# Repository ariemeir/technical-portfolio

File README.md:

# Technical Portfolio — Arie Meir

Representative projects, published for reference.

**→ [Browse all source on GitHub](https://github.com/ariemeir/technical-portfolio)**

## Projects

### [RoboImplant](roboimplant/) — non-invasive spinal implant adjustment system

A motorized orthopedic implant that lengthens a spinal distraction rod without
surgery, for treating early-onset scoliosis in growing children. Full-stack
across four disciplines:

- **Embedded** — AVR C firmware on an ATmega1284P: real-time motor control via a
  DS1267 digital pot into a maxon ESCON servo controller, interrupt-driven
  rotation counting, and current-threshold coupling detection as the primary
  safety interlock.
- **Mobile** — Android clinician console over Bluetooth SPP, with a custom
  line-oriented ASCII protocol, live telemetry, 3D visualization, and patient
  records.
- **Electronics** — EAGLE schematic and board layout for the controller,
  including the analog current/voltage sensing chain.
- **Mechanical** — SolidWorks enclosure for the handheld driver unit.

<p align="center">
  
  <br>
  <em>The handheld driver unit (v1)</em>
</p>

**→ [Read the one-page case study (PDF)](roboimplant/docs/roboimplant-case-study-arie-meir.pdf)**

Research prototype, ~2012–2013. Not a cleared medical device.
See [`roboimplant/NOTICE.md`](roboimplant/NOTICE.md) for rights and third-party
attribution.

---

### [3D Scanner](3dscanner/) — turntable photogrammetry rig

A DIY tabletop 3D scanner built to solve a real fabrication problem: an artist needed
larger and deeper variants of a commercially molded clay flower that existed only as a
physical object. It takes that object and produces a printable, watertight STL. Five
subsystems bound together by explicit contracts:

- **iOS** — **ScannerCam**, an iPhone camera server with a hand-rolled HTTP/1.1
  stack on `NWListener`: 13 REST routes, bearer auth with constant-time comparison,
  Keychain token storage, and hard locks on focus, exposure, and white balance.
  SwiftUI + AVFoundation, zero third-party packages.
- **Orchestration** — a Python session controller driving the scan loop across two
  machines, with idempotent retries, resumable sessions, and a five-stage SHA-256
  integrity chain from the phone's memory to the final archive.
- **Embedded** — an Arduino that controls the turntable by *impersonating its
  infrared remote*, replaying NEC codes reverse-engineered with a majority-vote
  capture sketch. No data port, no feedback, no encoder.
- **Reconstruction** — a Swift CLI over Apple Object Capture (RealityKit), chosen
  after COLMAP was tested and rejected for being CUDA-only on Apple Silicon.
- **Print prep** — a PyMeshLab pass that makes the mesh watertight, orients it by
  PCA, and scales it to real millimetres for printing and silicone-mold casting.

<p align="center">
  
  <br>
  <em>Input and output: the original ceramic dish, and a printed reproduction
  scanned from it.</em>
</p>

```
object ─→ 72 photos ─→ pose solve ─→ textured mesh ─→ watertight STL ─→ printed master
          locked        Object          USDZ/OBJ        PyMeshLab         silicone mold
          optics        Capture                         repair            → cast copies
```

The engineering centrepiece is control of an actuator that cannot be observed: the
turntable answers only to a fire-and-forget infrared *toggle*, so the controller
tracks an explicit assumed state and halts for human realignment on any ambiguity
rather than guessing and silently desynchronising the scan.

**→ [Read the one-page case study (PDF)](3dscanner/docs/3dscanner-case-study-arie-meir.pdf)**
· [Engineering log](3dscanner/docs/engineering-log.md)
· [Technical spec](3dscanner/docs/scannercam_spec.md)

Personal project, 2026. Working single-operator rig at late-prototype maturity.
See [`3dscanner/NOTICE.md`](3dscanner/NOTICE.md) for rights and attribution.

---

### [WifeSignal](wifesignal/) — a traffic light for the office door

A three-colour desk lamp that lets one person in the house tell another *how much
this can wait*. The office is a separate building: music on, windows closed, phone
face-down and unchecked for hours — which is the point, and which makes it a sealed
box. Text-and-hope fails when it matters; walking over always costs an interruption
whether or not the thing was urgent. The missing piece was never notification, it
was **priority expressed before the interruption happens**. Five components across
four disciplines:

- **iOS** — a SwiftUI app in 333 lines with no third-party packages and no
  Bluetooth: three priority buttons, a 5 s status poll, and a *Waiting… → Seen ♥*
  acknowledgement card that closes the loop for the sender.
- **Server** — a 290-line aiohttp + bleak bridge on a Mac, sharing one asyncio event
  loop, that exists because an iPhone cannot reliably be a BLE central for a device
  in another building. Bearer auth with constant-time comparison, exposed to a
  Tailscale tailnet only.
- **Embedded** — ESP32-C3 firmware over NimBLE exposing one service, one
  characteristic, one byte, with physical button presses as the acknowledgement path.
- **Electronics** — a custom two-layer KiCad board: three low-side lamp drivers,
  entirely through-hole, shaped and notched to match the enclosure.
- **Mechanical** — a 440-line Fusion 360 *script* that generates the two-part
  enclosure from derived dimensions, versioned in-band and guarded step by step.

<p align="center">
  
  <br>
  <em>Green — <strong>whenever you're free</strong>. The speaker beside it is the
  reason the project exists.</em>
</p>

```
tap ─→ HTTPS ─→ aiohttp ─→ 1 byte ─→ ESP32-C3 ─→ lamp ─→ physical ─→ "Seen ♥"
       tailnet   desired    over BLE   NimBLE              press       on her
       only      state                                     = ack       phone
```

The engineering centrepiece is the return path. Because the state characteristic is
bidirectional, three different events — the server's own write echoed back, a human
pressing the button, and a device that has drifted — all arrive as an identical
one-byte notification. They are separated with no timers, correlation IDs, or
sequence numbers: every notify is simply compared against the state the server
already intends, which collapses the whole problem into three branches and makes
recovery after a reboot or a reflash automatic.

**→ [Read the one-page case study (PDF)](wifesignal/docs/wifesignal-case-study-arie-meir.pdf)**
· [Full case study](wifesignal/) · [Server](wifesignal/server/) · [iOS app](wifesignal/app/)
· [Firmware](wifesignal/firmware/) · [Hardware](wifesignal/device/)

Personal project, 2026. In daily use.
See [`wifesignal/NOTICE.md`](wifesignal/NOTICE.md) for rights and attribution.

---

Each project directory carries its own README and rights notice. Unless stated
otherwise in a project's `NOTICE.md`, this work is published for reference only
and is not offered under an open-source license.

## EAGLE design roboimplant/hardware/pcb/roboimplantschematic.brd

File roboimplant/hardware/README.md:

# Hardware

**→ [Browse this directory on GitHub](https://github.com/ariemeir/technical-portfolio/tree/main/roboimplant/hardware)**
· [`pcb/`](https://github.com/ariemeir/technical-portfolio/tree/main/roboimplant/hardware/pcb)
· [`enclosure/`](https://github.com/ariemeir/technical-portfolio/tree/main/roboimplant/hardware/enclosure)

| | |
|:--:|:--:|
|  |  |
| **v1** — 3D-printed housing, acrylic top plate, brass inserts and drive coil. | **v2** — machined polycarbonate body with the controller electronics integrated alongside the coil assembly. |

The SolidWorks files below model the v1 unit on the left.

## `pcb/` — controller board

EAGLE 6.1 (CadSoft) design files for the board carrying the ATmega1284P, the
DS1267 digital potentiometer, the current/voltage sensing chain, the Bluetooth
module, and power management.

| File | |
|---|---|
| `roboimplantschematic.sch` | Schematic |
| `roboimplantschematic.brd` | Board layout |

**Viewing requires EAGLE 6.x or later** (now Autodesk EAGLE / Fusion Electronics).
Both files are EAGLE's XML format. No PDF export, gerbers, drill files, or BOM
were produced, so the design is not viewable or manufacturable directly from this
repository — exporting a schematic PDF would be the single highest-value addition.

## `enclosure/` — handheld driver housing

SolidWorks parts and assembly for the housing the clinician holds against the
patient.

| File | |
|---|---|
| `new_controller_enclosure_assembly.SLDASM` | Top-level assembly |
| `enclosure_bottom.SLDPRT` | Main body |
| `enclosure_circuit_cover.SLDPRT` | Electronics compartment cover |
| `enclosure_battery_cover.SLDPRT` | Battery compartment cover |
| `motor_top_cover.SLDDRW.SLDPRT` | Motor cover |
| `pcb.SLDPRT` | Board model, for fit-checking |
| `6mm_rod.SLDPRT` | Rod model |

**Requires SolidWorks.** No STEP, IGES, STL, or DXF exports were made.

Two known quirks, left as-found rather than tidied:

- `motor_top_cover.SLDDRW.SLDPRT` has a doubled extension from a save-as
  accident. It is a **part** file, not a drawing, and opens correctly as one —
  no `.SLDDRW` was ever preserved.
- The assembly stores references to its component files by name. If parts are
  renamed or moved, SolidWorks will report broken references and need them
  re-pointed.

## Motor controller

The board drives a **maxon ESCON 36/2 DC** servo controller (P/N 403112) via an
analog set-value input. Vendor documentation is in [`../docs/motor/`](../docs/motor/);
motor constants used by the firmware are in `firmware/config.h`.

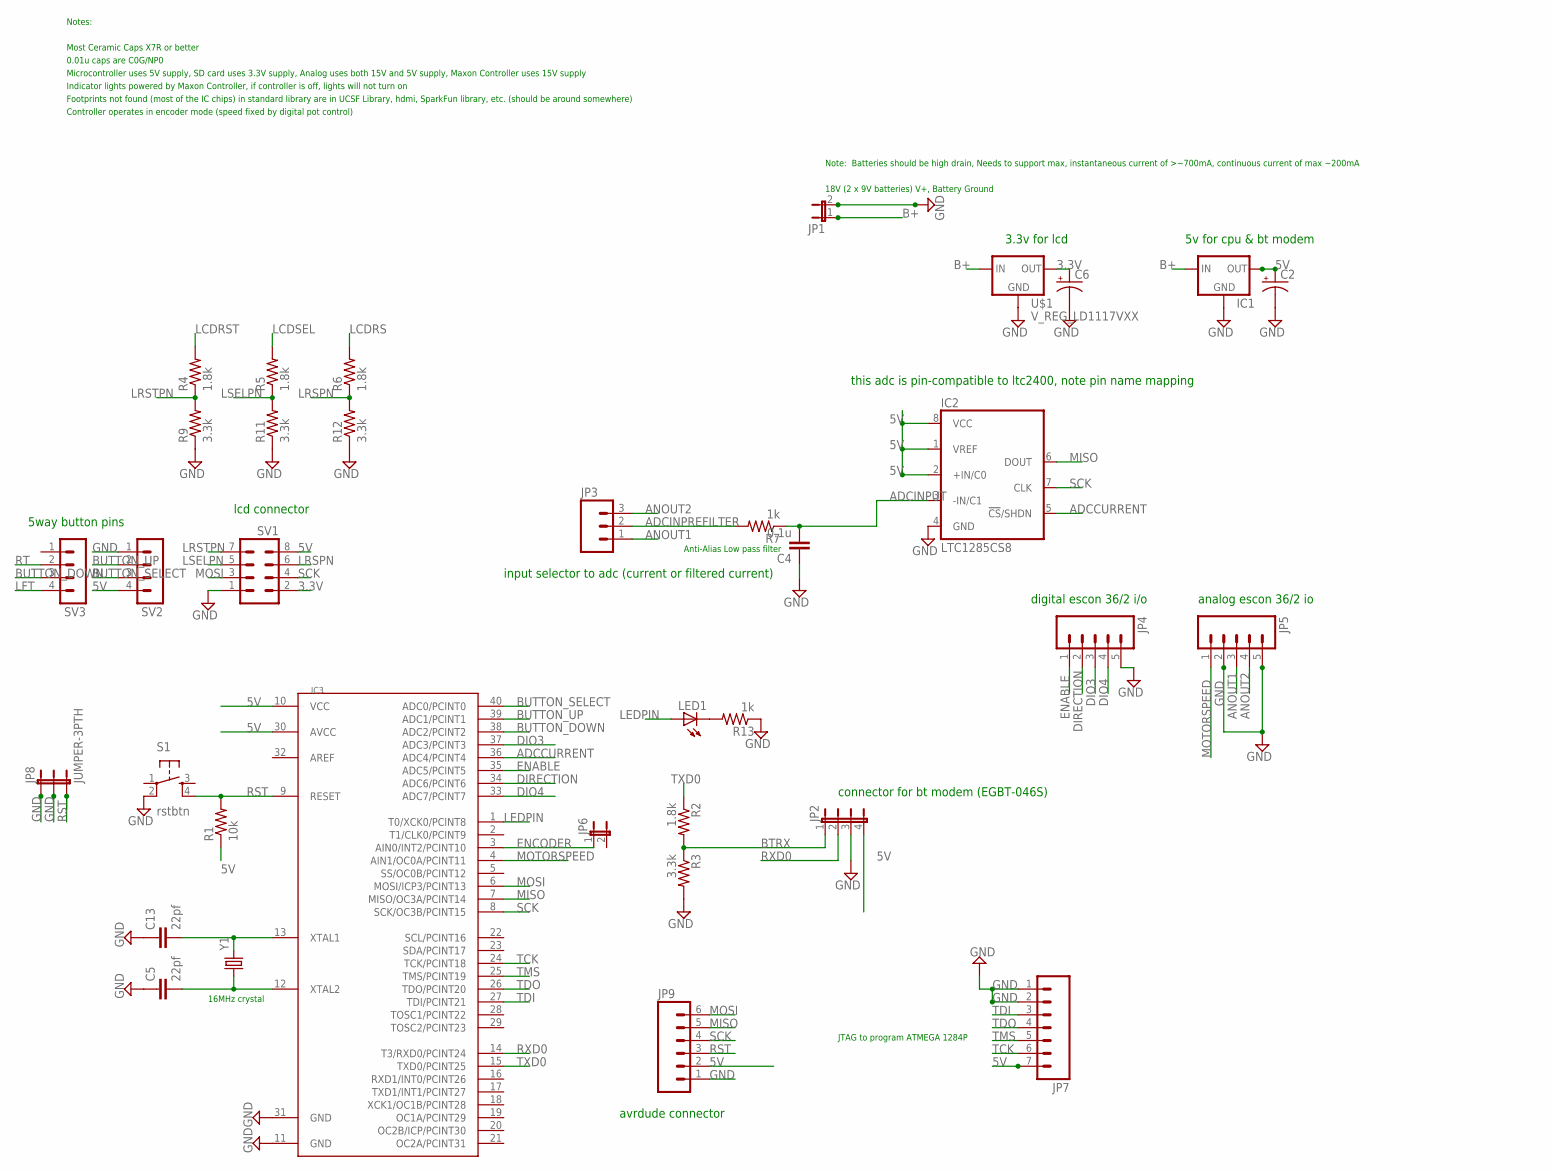
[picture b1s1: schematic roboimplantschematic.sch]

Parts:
C2, C6: CAP_POLPTH2; CPOL-RADIAL-10UF-25V
C4: 0.1u; 050X030_025
C5, C13: 22pf; 050X030_025
IC1: V_REG_78XX-TO-220; TO-220-ALT
IC2: LTC1285CS8; SOIC8
IC3: MEGA1284P; DIL40
JP1: JP1E; JP1
JP2: JP4E; JP4
JP3: M03LOCK_LONGPADS; 1X03_LOCK_LONGPADS
JP4, JP5: M05PTH_LONGPADS; 1X05_LONGPADS
JP6: JUMPER-2PTH; 1X02
JP7: M07LOCK; 1X07_LOCK
JP8: JUMPER-3PTH; 1X03
JP9: M06SIP_LOCK; 1X06-SIP_LOCK
LED1: LED5MM
R1: 10k; 0204/7
R2, R4, R5, R6: 1.8k; 0207/2V
R3, R9, R11, R12: 3.3k; 0207/2V
R7, R13: 1k; 0207/2V
S1: rstbtn; TACTILE-PTH
SV1: MA04-2
SV2, SV3: MA04-1
U$1: V_REG_LD1117VXX; 78XXL
Y1: CRYSTALHC49US; HC49US

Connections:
3.3V: C6.1 (+), SV1.2, U$1.GND (OUT)
5V: C2.1 (+), IC1.OUT, IC2.1 (VREF), IC2.2 (+IN/C0), IC2.8 (VCC), IC3.10 (VCC), IC3.30 (AVCC), JP2.4, JP7.7, JP9.2, R1.1, SV1.8, SV2.4
ADCCURRENT: IC2.5 (!CS!/SHDN), IC3.36 (ADC4/PCINT4)
ADCINPREFILTER: JP3.2, R7.2
ADCINPUT: C4.2, IC2.3 (-IN/C1), R7.1
ANOUT1: JP3.1, JP5.3
ANOUT2: JP3.3, JP5.4
B+: IC1.IN, JP1.1, U$1.OUT (IN)
BTRX: JP2.1, R2.2, R3.1
BUTTON_DOWN: IC3.38 (ADC2/PCINT2), SV3.3
BUTTON_SELECT: IC3.40 (ADC0/PCINT0), SV2.3
BUTTON_UP: IC3.39 (ADC1/PCINT1), SV2.2
DIO3: IC3.37 (ADC3/PCINT3), JP4.3
DIO4: IC3.33 (ADC7/PCINT7), JP4.4
DIRECTION: IC3.34 (ADC6/PCINT6), JP4.2
ENABLE: IC3.35 (ADC5/PCINT5), JP4.1
ENCODER: IC3.3 (AIN0/INT2/PCINT10), JP6.1
GND: C2.2 (-), C4.1, C5.1, C6.2 (-), C13.1, IC1.GND, IC2.4 (GND), IC3.11 (GND), IC3.31 (GND), JP1.2, JP2.3, JP4.5, JP5.2, JP5.5, JP7.1, JP7.2, JP8.1, JP8.2, JP9.1, R3.2, R9.1, R11.1, R12.1, R13.1, S1.2, SV1.1, SV2.1, U$1.IN (GND)
LCDRS: R6.2
LCDRST: R4.2
LCDSEL: R5.2
LEDPIN: IC3.1 (T0/XCK0/PCINT8), LED1.A
LFT: SV3.4
LRSPN: R6.1, R12.2, SV1.6
LRSTPN: R4.1, R9.2, SV1.7
LSELPN: R5.1, R11.2, SV1.5
MISO: IC2.6 (DOUT), IC3.7 (MISO/OC3A/PCINT14), JP9.5
MOSI: IC3.6 (MOSI/ICP3/PCINT13), JP9.6, SV1.3
MOTORSPEED: IC3.4 (AIN1/OC0A/PCINT11), JP5.1
unnamed: C5.2, IC3.12 (XTAL2), Y1.1
unnamed: C13.2, IC3.13 (XTAL1), Y1.2
unnamed: LED1.K (C), R13.2
RST: IC3.9 (RESET), JP8.3, JP9.3, R1.2, S1.4
RT: SV3.2
RXD0: IC3.14 (T3/RXD0/PCINT24), JP2.2
SCK: IC2.7 (CLK), IC3.8 (SCK/OC3B/PCINT15), JP9.4, SV1.4
TCK: IC3.24 (TCK/PCINT18), JP7.6
TDI: IC3.27 (TDI/PCINT21), JP7.3
TDO: IC3.26 (TDO/PCINT20), JP7.4
TMS: IC3.25 (TMS/PCINT19), JP7.5
TXD0: IC3.15 (TXD0/PCINT25), R2.1

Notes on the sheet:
18V (2 x 9V batteries) V+, Battery Ground
JTAG to program ATMEGA 1284P
Most Ceramic Caps X7R or better
Notes:
0.01u caps are C0G/NP0
Anti-Alias Low pass filter
Microcontroller uses 5V supply, SD card uses 3.3V supply, Analog uses both 15V and 5V supply, Maxon Controller uses 15V supply
Indicator lights powered by Maxon Controller, if controller is off, lights will not turn on
Footprints not found (most of the IC chips) in standard library are in UCSF Library, hdmi, SparkFun library, etc. (should be around somewhere)
16MHz crystal
Note: Batteries should be high drain, Needs to support max, instantaneous current of >~700mA, continuous current of max ~200mA
Controller operates in encoder mode (speed fixed by digital pot control)
connector for bt modem (EGBT-046S)
digital escon 36/2 i/o
analog escon 36/2 io
input selector to adc (current or filtered current)
3.3v for lcd
5v for cpu & bt modem
this adc is pin-compatible to ltc2400, note pin name mapping
lcd connector
5way button pins
avrdude connector

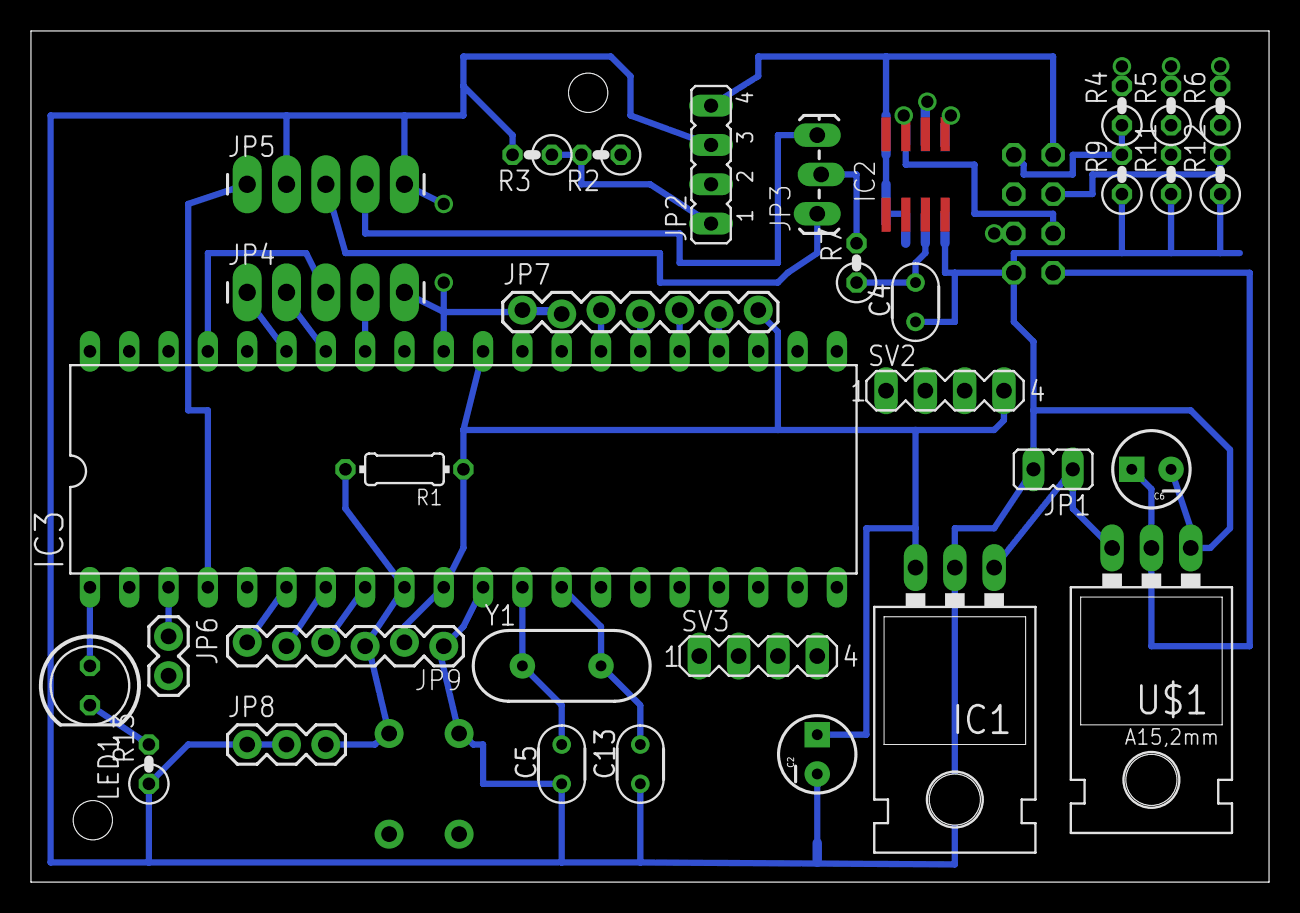
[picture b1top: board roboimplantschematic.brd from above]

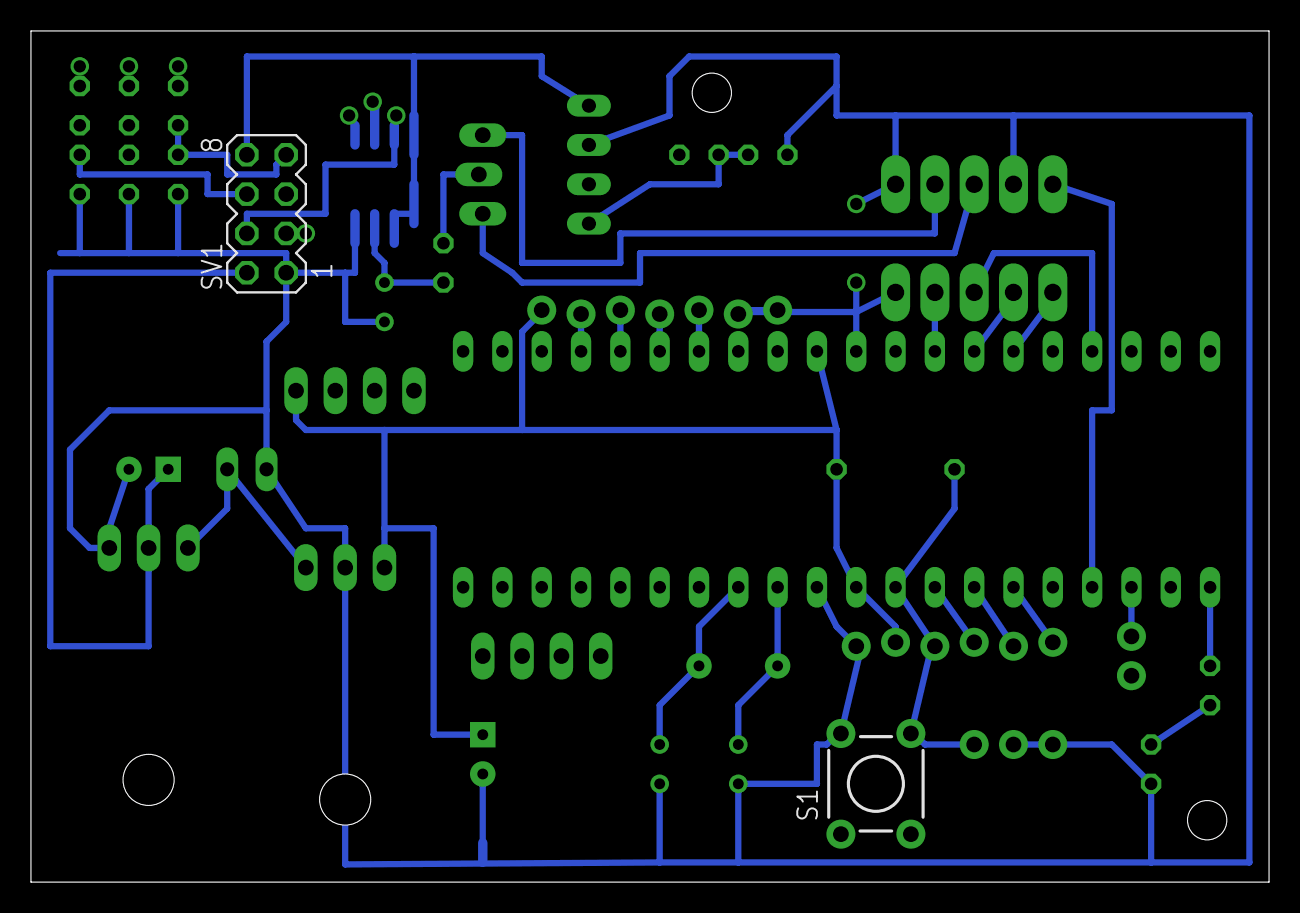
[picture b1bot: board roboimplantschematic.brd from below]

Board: 2 copper layers, 80.0 x 55.0 mm, 35 parts (2 on the bottom side), 36 nets.
